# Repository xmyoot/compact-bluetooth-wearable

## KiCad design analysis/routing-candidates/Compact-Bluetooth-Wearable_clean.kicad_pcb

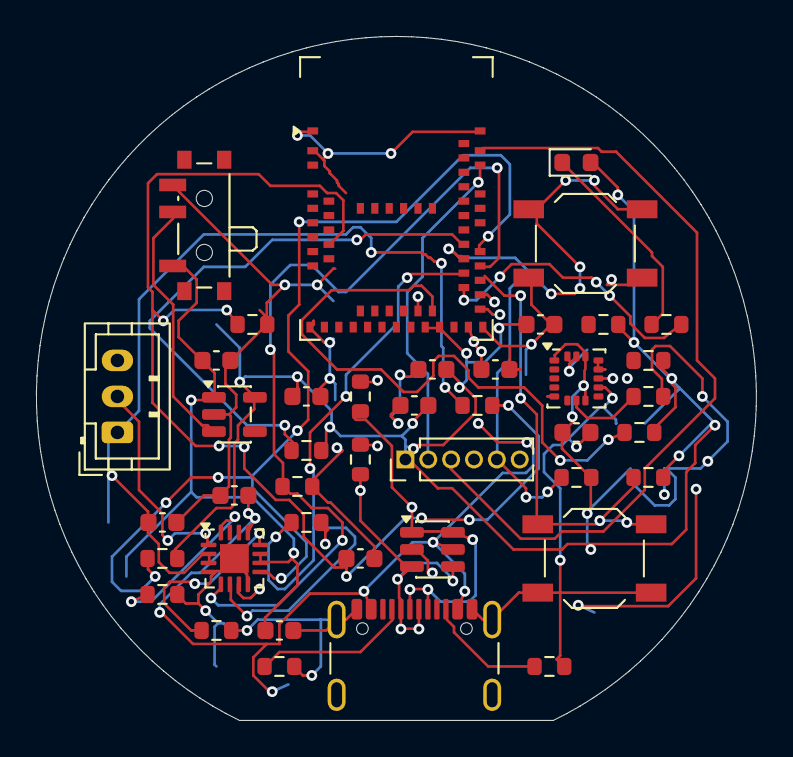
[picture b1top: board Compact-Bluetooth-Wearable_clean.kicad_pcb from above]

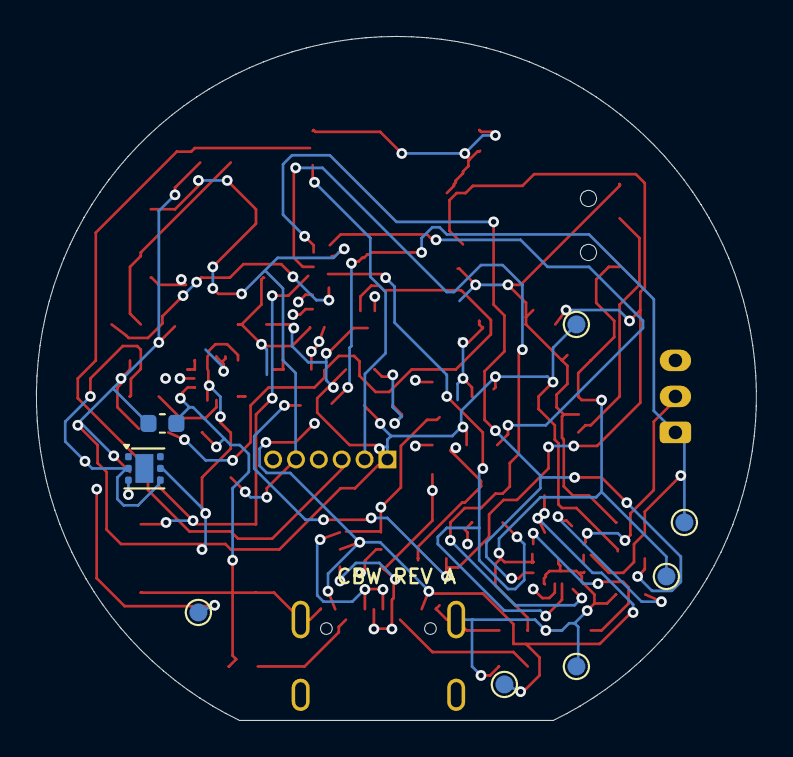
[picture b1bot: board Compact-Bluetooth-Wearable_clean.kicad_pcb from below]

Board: 4 copper layers, 40.0 x 38.0 mm, 50 parts (8 on the bottom side), 31 nets.

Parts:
C1, C5, C6: 10u; C_0603_1608Metric
C2, C9, C11, C12: 100n; C_0603_1608Metric
C3, C4: 4.7u; C_0603_1608Metric
C7, C8, C10: 1u; C_0603_1608Metric
D1: STATUS GREEN; LED_0603_1608Metric
D2: USBLC6-2SC6; SOT-23-6
J1: USB-C; USB4105_S1
J2: BATTERY + / NTC / -; JST_PH_B3B-PH-K_1x03_P2.00mm_Vertical
J3: SWD RECOVERY; PinHeader_1x06_P1.27mm_Vertical
R1, R2: 5.1k; R_0603_1608Metric
R3, R4: 27; R_0603_1608Metric
R5: 8.87k; R_0603_1608Metric
R6: 3.32k; R_0603_1608Metric
R7, R8, R9, R10, R13, R14, R15, R19: 100k; R_0603_1608Metric
R11, R12: 4.7k; R_0603_1608Metric
R16: 1k; R_0603_1608Metric
R17, R18: 1M; R_0603_1608Metric
SW1: POWER; SW_SPDT_PCM12
SW2: USER / DFU; SW_SPST_TL3342
SW3: RESET; SW_SPST_TL3342
TP1: GND; TestPoint_Pad_D1.0mm
TP2: VBUS; TestPoint_Pad_D1.0mm
TP3: VBAT; TestPoint_Pad_D1.0mm
TP4: VSYS; TestPoint_Pad_D1.0mm
TP5: +3V0; TestPoint_Pad_D1.0mm
TP6: ACC_INT; TestPoint_Pad_D1.0mm
U1: MDBT50Q-1MV2; Raytac_MDBT50Q
U2: BQ24074RGTR; VQFN-16-1EP_3x3mm_P0.5mm_EP1.6x1.6mm
U3: TPS7A2030PDBVR; SOT-23-5
U4: LIS3DHTR; LGA-16_3x3mm_P0.5mm_LayoutBorder3x5y
U5: TMP117AIDRVR; TMP117_NoPasteEP

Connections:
+3V0: C1.1, C2.1, C8.1, C9.1, C10.1, C11.1, D1.2, J3.1, R9.2, R10.2, R11.2, R12.2, R13.2, R14.2, R15.2, TP5.1, U1.28, U1.30, U3.5, U4.1, U4.8, U4.14, U5.5
ACC_INT: TP6.1, U1.27, U4.11
ACC_SA0: R19.1, U4.7
BAT_NTC: J2.2, U2.1
BAT_SENSE: C12.1, R17.2, R18.1, U1.11
CC1: J1.A5, R1.1
CC2: J1.B5, R2.1
CHARGE_N: R10.1, U1.41, U2.9
CHG_EN1: R7.1, U1.38, U2.6
CHG_EN2: R8.1, U1.39, U2.5
GND: C1.2, C2.2, C3.2, C4.2, C5.2, C6.2, C7.2, C8.2, C9.2, C10.2, C11.2, C12.2, D2.2, J1.A1, J1.A12, J1.B1, J1.B12, J1.S1, J2.3, J3.4, J3.6, R1.2, R2.2, R5.2, R6.2, R7.2, R8.2, R18.2, R19.2, SW1.3, SW2.2, SW3.2, TP1.1, U1.1, U1.2, U1.15, U1.33, U1.55, U2.4, U2.8, U2.17, U3.2, U4.5, U4.10, U4.12, U4.13, U4.15, U4.16, U5.2, U5.4
I2C_SCL: R11.1, U1.16, U4.4, U5.1
I2C_SDA: R12.1, U1.19, U4.6, U5.6
ILIM: R6.1, U2.12
ISET: R5.1, U2.16
LED_K: D1.1, R16.1
LED_STATUS: R16.2, U1.36
PGOOD_N: R9.1, U1.42, U2.7
POWER_EN: SW1.2, U3.3
RESET_N: J3.5, R15.1, SW3.1, U1.40
SWCLK: J3.3, U1.53
SWDIO: J3.2, U1.51
TEMP_ALERT: R13.1, U1.29, U5.3
USB_CONN_N: D2.3, D2.4, J1.A7, J1.B7, R4.1
USB_CONN_P: D2.1, D2.6, J1.A6, J1.B6, R3.1
USB_N: R4.2, U1.34
USB_P: R3.2, U1.35
USER_N: R14.1, SW2.1, U1.37
VBAT: C5.1, J2.1, R17.1, TP3.1, U2.2, U2.3
VBUS: C3.1, C4.1, D2.5, J1.A4, J1.A9, J1.B4, J1.B9, TP2.1, U1.32, U2.13
VSYS: C6.1, C7.1, SW1.1, TP4.1, U2.10, U2.11, U3.1
